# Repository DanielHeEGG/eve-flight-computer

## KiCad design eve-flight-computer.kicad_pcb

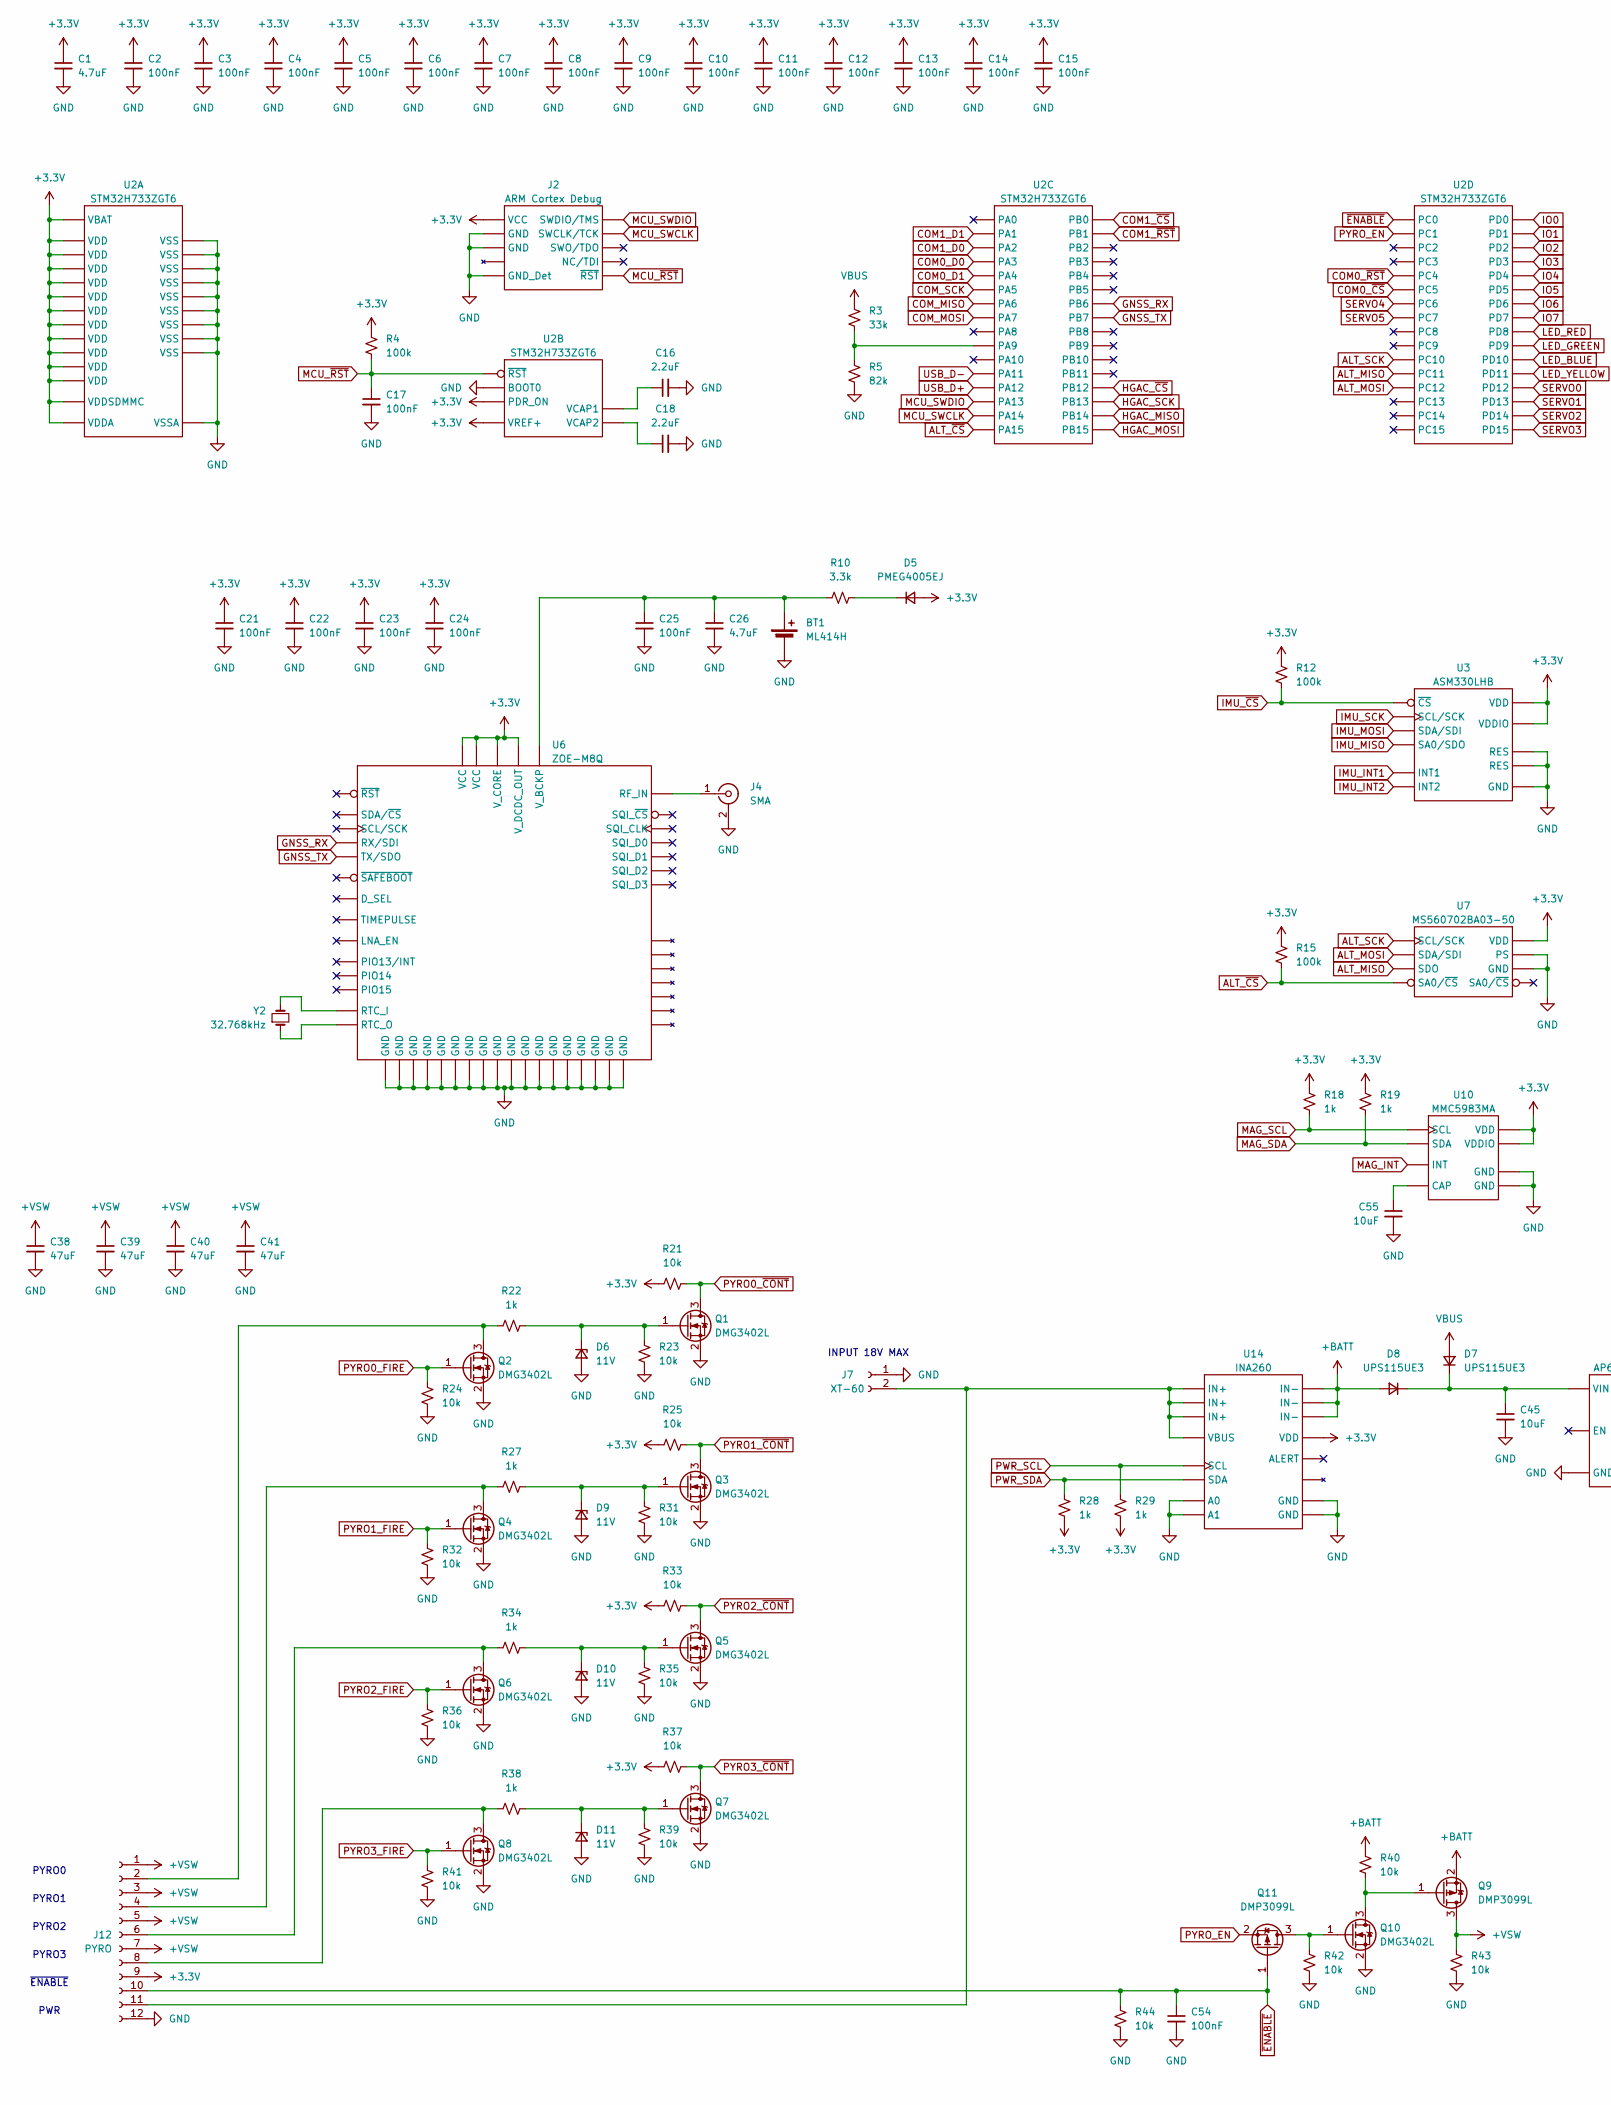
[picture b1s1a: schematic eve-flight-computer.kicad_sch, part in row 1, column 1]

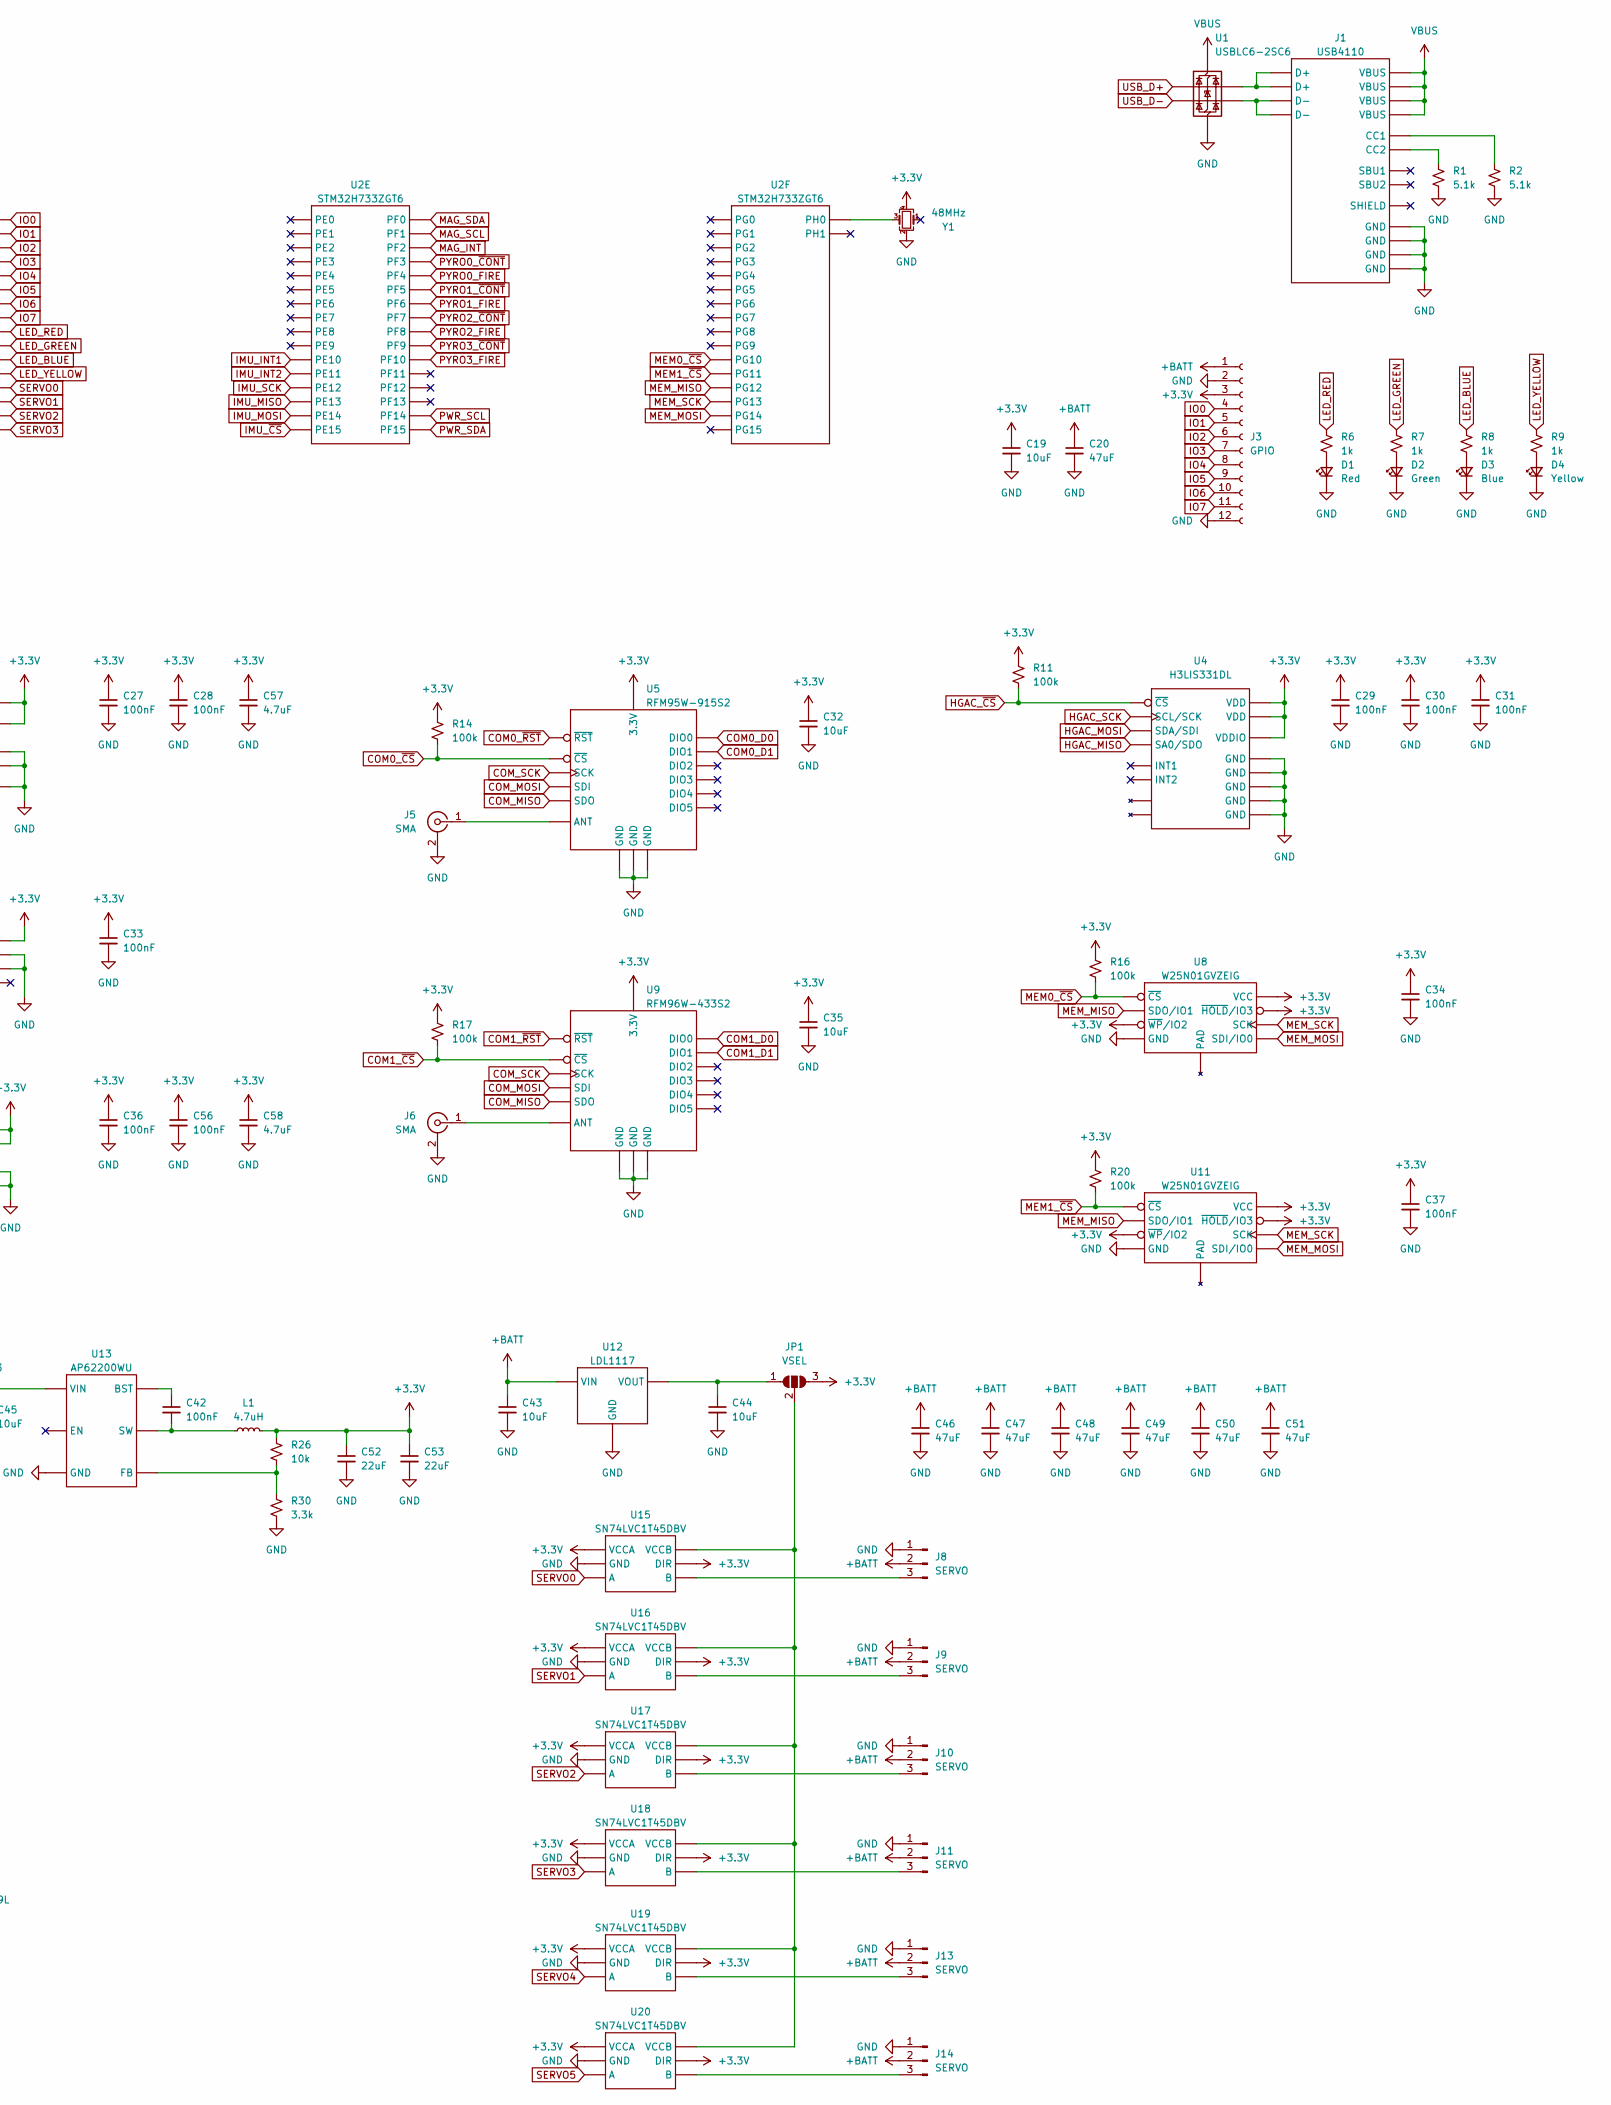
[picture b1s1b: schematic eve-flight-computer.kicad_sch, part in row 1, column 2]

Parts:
BT1: ML414H; Part # ML414H-IV01E
C1, C26, C57, C58: 4.7uF; 0402_1005M; Part # Generic 4.7uF 6.3V X5R 0402 MLCC
C2, C3, C4, C5, C6, C7, C8, C9, C10, C11, C12, C13, C14, C15, C17, C21, C22, C23, C24, C25, C27, C28, C29, C30, C31, C33, C34, C36, C37, C42, C54, C56: 100nF; 0402_1005M; Part # Generic 100nF 25V X7R 0402 MLCC
C16, C18: 2.2uF; 0402_1005M; Part # Generic 2.2uF 6.3V X5R 0402 MLCC
C19, C32, C35, C43, C44, C45, C55: 10uF; 0805_2012M; Part # Generic 10uF 25V X5R 0805 MLCC
C20, C38, C39, C40, C41, C46, C47, C48, C49, C50, C51: 47uF; C_1206_3216Metric; Part # Generic 47uF 25V X5R 1206 MLCC
C52, C53: 22uF; 0805_2012M; Part # Generic 22uF 6.3V X5R 0805 MLCC
D1: Red; D_0603_1608Metric; Part # Generic Red 0603 LED
D2: Green; D_0603_1608Metric; Part # Generic Green 0603 LED
D3: Blue; D_0603_1608Metric; Part # Generic Blue 0603 LED
D4: Yellow; D_0603_1608Metric; Part # Generic Yellow 0603 LED
D5: PMEG4005EJ; D_SOD-323; Part # PMEG4005EJ
D6, D9, D10, D11: 11V; D_SOD-123; Part # MMSZ11T1G
D7, D8: UPS115UE3; D_Powermite_AK; Part # UPS115UE3/TR7
J1: USB4110; USB_C_Receptacle_GCT_USB4110; Part # USB4110-GF-A
J2: ARM Cortex Debug; PinHeader_2x05_P1.27mm_Vertical_SMD; Part # 20021121-00010C4LF
J3: GPIO; PinSocket_1x12_P2.54mm_Vertical; Part # 1-282834-2
J4, J5, J6: SMA; SMA_Amphenol_132289_EdgeMount; Part # 132289
J7: XT-60; XT60PW-M; Part # XT60PW-M
J8, J9, J10, J11, J13, J14: SERVO; JST_XH_B3B-XH-A_1x03_P2.50mm_Vertical; Part # B3B-XH-A
J12: PYRO; PinSocket_1x12_P2.54mm_Vertical; Part # 1-282834-2
JP1: VSEL; SolderJumper-3_P1.3mm_Open_Pad1.0x1.5mm
L1: 4.7uH; L_1210_3225Metric; Part # DFE322520FD-4R7M
Q1, Q2, Q3, Q4, Q5, Q6, Q7, Q8, Q10: DMG3402L; SOT-23-3; Part # DMG3402L-7
Q9, Q11: DMP3099L; SOT-23-3; Part # DMP3099L-7
R1, R2: 5.1k; 0402_1005M; Part # Generic 5.1k 1% 0402 Chip Resistor
R3: 33k; 0402_1005M; Part # Generic 33k 1% 0402 Chip Resistor
R4, R11, R12, R14, R15, R16, R17, R20: 100k; 0402_1005M; Part # Generic 100k 1% 0402 Chip Resistor
R5: 82k; 0402_1005M; Part # Generic 82k 1% 0402 Chip Resistor
R6, R7, R8, R9, R18, R19, R22, R27, R28, R29, R34, R38: 1k; 0402_1005M; Part # Generic 1k 1% 0402 Chip Resistor
R10, R30: 3.3k; 0402_1005M; Part # Generic 3.3k 1% 0402 Chip Resistor
R21, R23, R24, R25, R26, R31, R32, R33, R35, R36, R37, R39, R40, R41, R42, R43, R44: 10k; 0402_1005M; Part # Generic 10k 1% 0402 Chip Resistor
U1: USBLC6-2SC6; SOT-23-6; Part # USBLC6-2SC6
U2: STM32H733ZGT6; LQFP-144_20x20mm_P0.5mm; Part # STM32H733ZGT6
U3: ASM330LHB; LGA-14_3x2.5mm_P0.5mm_LayoutBorder3x4y; Part # ASM330LHBTR
U4: H3LIS331DL; LGA-16_3x3mm_P0.5mm_LayoutBorder3x5y; Part # H3LIS331DLTR
U5: RFM95W-915S2; RFM9xW-xxxS2; Part # RFM95W-915S2
U6: ZOE-M8Q; Part # ZOE-M8Q-0
U7: MS560702BA03-50; MS5607-02BA; Part # MS560702BA03-50
U8, U11: W25N01GVZEIG; WSON-8-1EP_8x6mm_P1.27mm_EP3.4x4.3mm; Part # W25N01GVZEIG
U9: RFM96W-433S2; RFM9xW-xxxS2; Part # RFM96W-433S2
U10: MMC5983MA; LGA-16_3x3mm_P0.5mm; Part # MMC5983MA
U12: LDL1117; SOT-223-3_TabPin2; Part # LDL1117S50R
U13: AP62200WU; SOT-23-6; Part # AP62200WU-7
U14: INA260; TSSOP-16_4.4x5mm_P0.65mm; Part # INA260AIPWR
U15, U16, U17, U18, U19, U20: SN74LVC1T45DBV; SOT-23-6; Part # SN74LVC1T45DBV
Y1: 48MHz; Crystal_SMD_2520-4Pin_2.5x2.0mm; Part # ECS-2520MV-480-CN-TR
Y2: 32.768kHz; Crystal_SMD_MicroCrystal_CM9V-T1A-2Pin_1.6x1.0mm; Part # CM9V-T1A-32.768KHZ-7PF-100PPM-TA-QC

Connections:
+3.3V: C1.1, C2.1, C3.1, C4.1, C5.1, C6.1, C7.1, C8.1, C9.1, C10.1, C11.1, C12.1, C13.1, C14.1, C15.1, C19.1, C21.1, C22.1, C23.1, C24.1, C27.1, C28.1, C29.1, C30.1, C31.1, C32.1, C33.1, C34.1, C35.1, C36.1, C37.1, C52.1, C53.1, C56.1, C57.1, C58.1, D5.2 (A), J2.1 (VCC), J3.3, J12.9, JP1.3 (B), L1.2, R4.1, R11.1, R12.1, R14.1, R15.1, R16.1, R17.1, R18.1, R19.1, R20.1, R21.1, R25.1, R26.1, R28.2, R29.2, R33.1, R37.1, U2.6 (VBAT), U2.17 (VDD), U2.30 (VDD), U2.32 (VREF+), U2.33 (VDDA), U2.39 (VDD), U2.52 (VDD), U2.62 (VDD), U2.72 (VDD), U2.84 (VDD), U2.95 (VDD), U2.108 (VDD), U2.121 (VDDSDMMC), U2.131 (VDD), U2.143 (PDR_ON), U2.144 (VDD), U3.5 (VDDIO), U3.8 (VDD), U4.1 (VDDIO), U4.14 (VDD), U4.15 (VDD), U5.13 (3.3V), U6.G1 (V_CORE), U6.H1 (V_DCDC_OUT), U6.J1 (VCC), U6.J2 (VCC), U7.1 (VDD), U8.3 (~WP/IO2), U8.7 (~HOLD/IO3), U8.8 (VCC), U9.13 (3.3V), U10.2 (VDD), U10.13 (VDDIO), U11.3 (~WP/IO2), U11.7 (~HOLD/IO3), U11.8 (VCC), U14.10 (VDD), U15.1 (VCCA), U15.5 (DIR), U16.1 (VCCA), U16.5 (DIR), U17.1 (VCCA), U17.5 (DIR), U18.1 (VCCA), U18.5 (DIR), U19.1 (VCCA), U19.5 (DIR), U20.1 (VCCA), U20.5 (DIR), Y1.4
+BATT: C20.1, C43.1, C46.1, C47.1, C48.1, C49.1, C50.1, C51.1, D8.2 (A), J3.1, J8.2, J9.2, J10.2, J11.2, J13.2, J14.2, Q9.2 (S), R40.1, U12.3 (VIN), U14.14 (IN-), U14.15 (IN-), U14.16 (IN-)
+VSW: C38.1, C39.1, C40.1, C41.1, J12.1, J12.3, J12.5, J12.7, Q9.3 (D), R43.1
ALT_MISO: U2.112 (PC11), U7.6 (SDO)
ALT_MOSI: U2.113 (PC12), U7.7 (SDA/SDI)
ALT_SCK: U2.111 (PC10), U7.8 (SCL/SCK)
ALT_~CS: R15.2, U2.110 (PA15), U7.5 (SA0/~CS)
COM0_D0: U2.37 (PA3), U5.14 (DIO0)
COM0_D1: U2.40 (PA4), U5.15 (DIO1)
COM0_~CS: R14.2, U2.45 (PC5), U5.5 (~CS)
COM0_~RST: U2.44 (PC4), U5.6 (~RST)
COM1_D0: U2.36 (PA2), U9.14 (DIO0)
COM1_D1: U2.35 (PA1), U9.15 (DIO1)
COM1_~CS: R17.2, U2.46 (PB0), U9.5 (~CS)
COM1_~RST: U2.47 (PB1), U9.6 (~RST)
COM_MISO: U2.42 (PA6), U5.2 (SDO), U9.2 (SDO)
COM_MOSI: U2.43 (PA7), U5.3 (SDI), U9.3 (SDI)
COM_SCK: U2.41 (PA5), U5.4 (SCK), U9.4 (SCK)
GND: BT1.2 (-), C1.2, C2.2, C3.2, C4.2, C5.2, C6.2, C7.2, C8.2, C9.2, C10.2, C11.2, C12.2, C13.2, C14.2, C15.2, C16.2, C17.2, C18.2, C19.2, C20.2, C21.2, C22.2, C23.2, C24.2, C25.2, C26.2, C27.2, C28.2, C29.2, C30.2, C31.2, C32.2, C33.2, C34.2, C35.2, C36.2, C37.2, C38.2, C39.2, C40.2, C41.2, C43.2, C44.2, C45.2, C46.2, C47.2, C48.2, C49.2, C50.2, C51.2, C52.2, C53.2, C54.2, C55.2, C56.2, C57.2, C58.2, D1.1 (K), D2.1 (K), D3.1 (K), D4.1 (K), D6.2 (A), D9.2 (A), D10.2 (A), D11.2 (A), J1.A1 (GND), J1.A12 (GND), J1.B1 (GND), J1.B12 (GND), J2.3 (GND), J2.5 (GND), J2.9 (GND_Det), J3.2, J3.12, J4.2 (Ext), J5.2 (Ext), J6.2 (Ext), J7.1, J8.1, J9.1, J10.1, J11.1, J12.12, J13.1, J14.1, Q1.2 (S), Q2.2 (S), Q3.2 (S), Q4.2 (S), Q5.2 (S), Q6.2 (S), Q7.2 (S), Q8.2 (S), Q10.2 (S), R1.2, R2.2, R5.2, R23.2, R24.2, R30.2, R31.2, R32.2, R35.2, R36.2, R39.2, R41.2, R42.2, R43.2, R44.2, U1.2, U2.16 (VSS), U2.31 (VSSA), U2.38 (VSS), U2.51 (VSS), U2.61 (VSS), U2.83 (VSS), U2.94 (VSS), U2.107 (VSS), U2.120 (VSS), U2.130 (VSS), U2.138 (BOOT0), U3.2 (RES), U3.3 (RES), U3.7 (GND), U4.5 (GND), U4.10 (GND), U4.12 (GND), U4.13 (GND), U4.16 (GND), U5.1 (GND), U5.8 (GND), U5.10 (GND), U6.A1 (GND), U6.A3 (GND), U6.A5 (GND), U6.A7 (GND), U6.A8 (GND), U6.A9 (GND), U6.B9 (GND), U6.C7 (GND), U6.C9 (GND), U6.D6 (GND), U6.D9 (GND), U6.E7 (GND), U6.F7 (GND), U6.G3 (GND), U6.G6 (GND), U6.G7 (GND), U6.J3 (GND), U6.J9 (GND), U7.2 (PS), U7.3 (GND), U8.4 (GND), U9.1 (GND), U9.8 (GND), U9.10 (GND), U10.9 (GND), U10.11 (GND), U11.4 (GND), U12.1 (GND), U13.1 (GND), U14.4 (A1), U14.5 (A0), U14.6 (GND), U14.11 (GND), U15.2 (GND), U16.2 (GND), U17.2 (GND), U18.2 (GND), U19.2 (GND), U20.2 (GND), Y1.2
GNSS_RX: U2.136 (PB6), U6.J4 (RX/SDI)
GNSS_TX: U2.137 (PB7), U6.J5 (TX/SDO)
HGAC_MISO: U2.75 (PB14), U4.7 (SA0/SDO)
HGAC_MOSI: U2.76 (PB15), U4.6 (SDA/SDI)
HGAC_SCK: U2.74 (PB13), U4.4 (SCL/SCK)
HGAC_~CS: R11.2, U2.73 (PB12), U4.8 (~CS)
IMU_INT1: U2.63 (PE10), U3.4 (INT1)
IMU_INT2: U2.64 (PE11), U3.9 (INT2)
IMU_MISO: U2.66 (PE13), U3.1 (SA0/SDO)
IMU_MOSI: U2.67 (PE14), U3.14 (SDA/SDI)
IMU_SCK: U2.65 (PE12), U3.13 (SCL/SCK)
IMU_~CS: R12.2, U2.68 (PE15), U3.12 (~CS)
IO0: J3.4, U2.114 (PD0)
IO1: J3.5, U2.115 (PD1)
IO2: J3.6, U2.116 (PD2)
IO3: J3.7, U2.117 (PD3)
IO4: J3.8, U2.118 (PD4)
IO5: J3.9, U2.119 (PD5)
IO6: J3.10, U2.122 (PD6)
IO7: J3.11, U2.123 (PD7)
LED_BLUE: R8.1, U2.79 (PD10)
LED_GREEN: R7.1, U2.78 (PD9)
LED_RED: R6.1, U2.77 (PD8)
LED_YELLOW: R9.1, U2.80 (PD11)
MAG_INT: U2.12 (PF2), U10.15 (INT)
MAG_SCL: R18.2, U2.11 (PF1), U10.1 (SCL)
MAG_SDA: R19.2, U2.10 (PF0), U10.16 (SDA)
MCU_SWCLK: J2.4 (SWCLK/TCK), U2.109 (PA14)
MCU_SWDIO: J2.2 (SWDIO/TMS), U2.105 (PA13)
MCU_~RST: C17.1, J2.10 (~RST), R4.2, U2.25 (~RST)
MEM0_~CS: R16.2, U2.125 (PG10), U8.1 (~CS)
MEM1_~CS: R20.2, U2.126 (PG11), U11.1 (~CS)
MEM_MISO: U2.127 (PG12), U8.2 (SDO/IO1), U11.2 (SDO/IO1)
MEM_MOSI: U2.129 (PG14), U8.5 (SDI/IO0), U11.5 (SDI/IO0)
MEM_SCK: U2.128 (PG13), U8.6 (SCK), U11.6 (SCK)
unnamed: BT1.1 (+), C25.1, C26.1, R10.1, U6.H9 (V_BCKP)
unnamed: D1.2 (A), R6.2
unnamed: D2.2 (A), R7.2
unnamed: D3.2 (A), R8.2
unnamed: D4.2 (A), R9.2
unnamed: D5.1 (K), R10.2
unnamed: D6.1 (K), Q1.1 (G), R22.2, R23.1
unnamed: C45.1, D7.1 (K), D8.1 (K), U13.3 (VIN)
unnamed: D9.1 (K), Q3.1 (G), R27.2, R31.1
unnamed: D10.1 (K), Q5.1 (G), R34.2, R35.1
unnamed: D11.1 (K), Q7.1 (G), R38.2, R39.1
unnamed: J1.A5 (CC1), R2.1
unnamed: J1.B5 (CC2), R1.1
unnamed: J1.A6 (D+), J1.B6 (D+), U1.6
unnamed: J1.A7 (D-), J1.B7 (D-), U1.4
unnamed: J4.1 (In), U6.A4 (RF_IN)
unnamed: J5.1 (In), U5.9 (ANT)
unnamed: J6.1 (In), U9.9 (ANT)
unnamed: J8.3, U15.4 (B)
unnamed: J9.3, U16.4 (B)
unnamed: J10.3, U17.4 (B)
unnamed: J11.3, U18.4 (B)
unnamed: J12.2, Q2.3 (D), R22.1
unnamed: J12.4, Q4.3 (D), R27.1
unnamed: J12.6, Q6.3 (D), R34.1
unnamed: J12.8, Q8.3 (D), R38.1
unnamed: J7.2, J12.11, U14.1 (IN+), U14.2 (IN+), U14.3 (IN+), U14.12 (VBUS)
unnamed: J13.3, U19.4 (B)
unnamed: J14.3, U20.4 (B)
unnamed: C44.1, JP1.1 (A), U12.2 (VOUT)
unnamed: JP1.2 (C), U15.6 (VCCB), U16.6 (VCCB), U17.6 (VCCB), U18.6 (VCCB), U19.6 (VCCB), U20.6 (VCCB)
unnamed: Q9.1 (G), Q10.3 (D), R40.2
unnamed: Q10.1 (G), Q11.3 (D), R42.1
unnamed: C16.1, U2.71 (VCAP1)
unnamed: C18.1, U2.106 (VCAP2)
unnamed: R3.2, R5.1, U2.101 (PA9)
unnamed: U2.23 (PH0), Y1.3
unnamed: U6.J7 (RTC_I), Y2.2
unnamed: U6.J8 (RTC_O), Y2.1
unnamed: C55.1, U10.10 (CAP)
unnamed: C42.1, U13.6 (BST)
unnamed: R26.2, R30.1, U13.4 (FB)
unnamed: C42.2, L1.1, U13.2 (SW)
PWR_SCL: R29.1, U2.54 (PF14), U14.9 (SCL)
PWR_SDA: R28.1, U2.55 (PF15), U14.8 (SDA)
PYRO0_FIRE: Q2.1 (G), R24.1, U2.14 (PF4)
PYRO0_~CONT: Q1.3 (D), R21.2, U2.13 (PF3)
PYRO1_FIRE: Q4.1 (G), R32.1, U2.18 (PF6)
PYRO1_~CONT: Q3.3 (D), R25.2, U2.15 (PF5)
PYRO2_FIRE: Q6.1 (G), R36.1, U2.20 (PF8)
PYRO2_~CONT: Q5.3 (D), R33.2, U2.19 (PF7)
PYRO3_FIRE: Q8.1 (G), R41.1, U2.22 (PF10)
PYRO3_~CONT: Q7.3 (D), R37.2, U2.21 (PF9)
PYRO_EN: Q11.2 (S), U2.27 (PC1)
SERVO0: U2.81 (PD12), U15.3 (A)
SERVO1: U2.82 (PD13), U16.3 (A)
SERVO2: U2.85 (PD14), U17.3 (A)
SERVO3: U2.86 (PD15), U18.3 (A)
SERVO4: U2.96 (PC6), U19.3 (A)
SERVO5: U2.97 (PC7), U20.3 (A)
USB_D+: U1.1, U2.104 (PA12)
USB_D-: U1.3, U2.103 (PA11)
VBUS: D7.2 (A), J1.A4 (VBUS), J1.A9 (VBUS), J1.B4 (VBUS), J1.B9 (VBUS), R3.1, U1.5
~ENABLE: C54.1, J12.10, Q11.1 (G), R44.1, U2.26 (PC0)

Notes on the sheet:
~{ENABLE}
INPUT 18V MAX
PYRO3
PWR
PYRO1
PYRO2
PYRO0

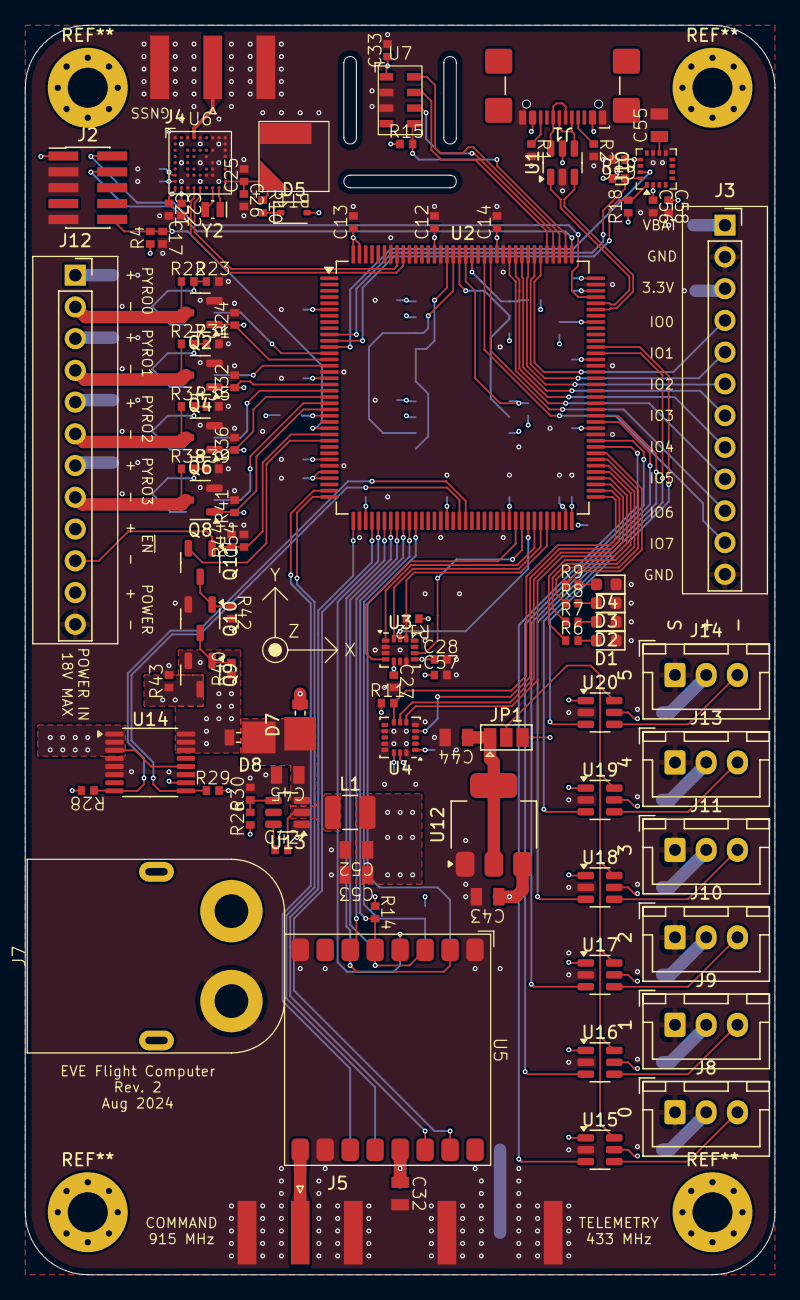
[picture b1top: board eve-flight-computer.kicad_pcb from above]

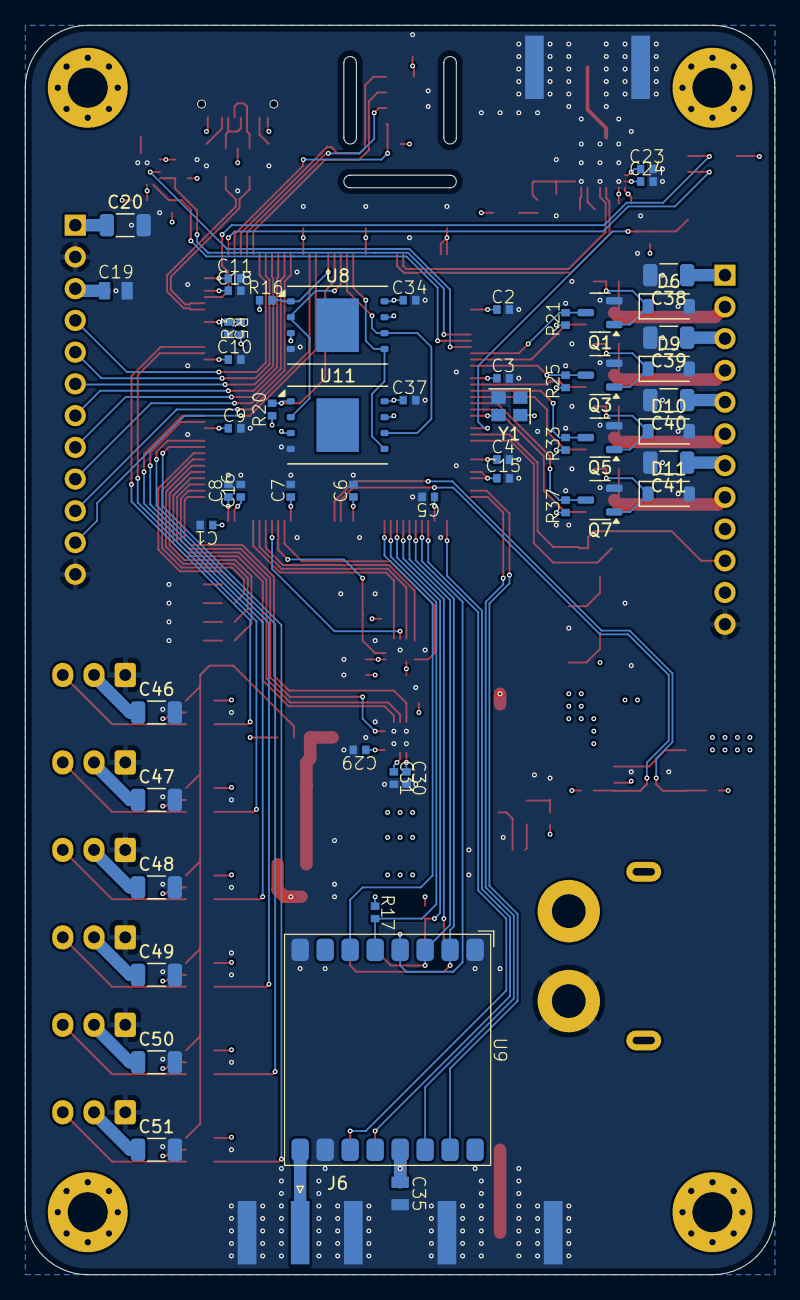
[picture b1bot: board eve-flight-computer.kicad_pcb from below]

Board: 6 copper layers, 60.0 x 100.0 mm, 162 parts (56 on the bottom side), 118 nets.

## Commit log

2024-07-06 Design file setup, add design rules
2024-08-28 Rev. 1
2024-09-11 Rev. 2
